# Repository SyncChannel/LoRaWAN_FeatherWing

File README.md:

# LoRaWAN_FeatherWing
Add the MicroChip RN2483/RN2903 LoRaWAN module to Adafruit Feather

http://syncchannel.blogspot.com/2016/06/lorawan-featherwing-for-adafruit-feather.html

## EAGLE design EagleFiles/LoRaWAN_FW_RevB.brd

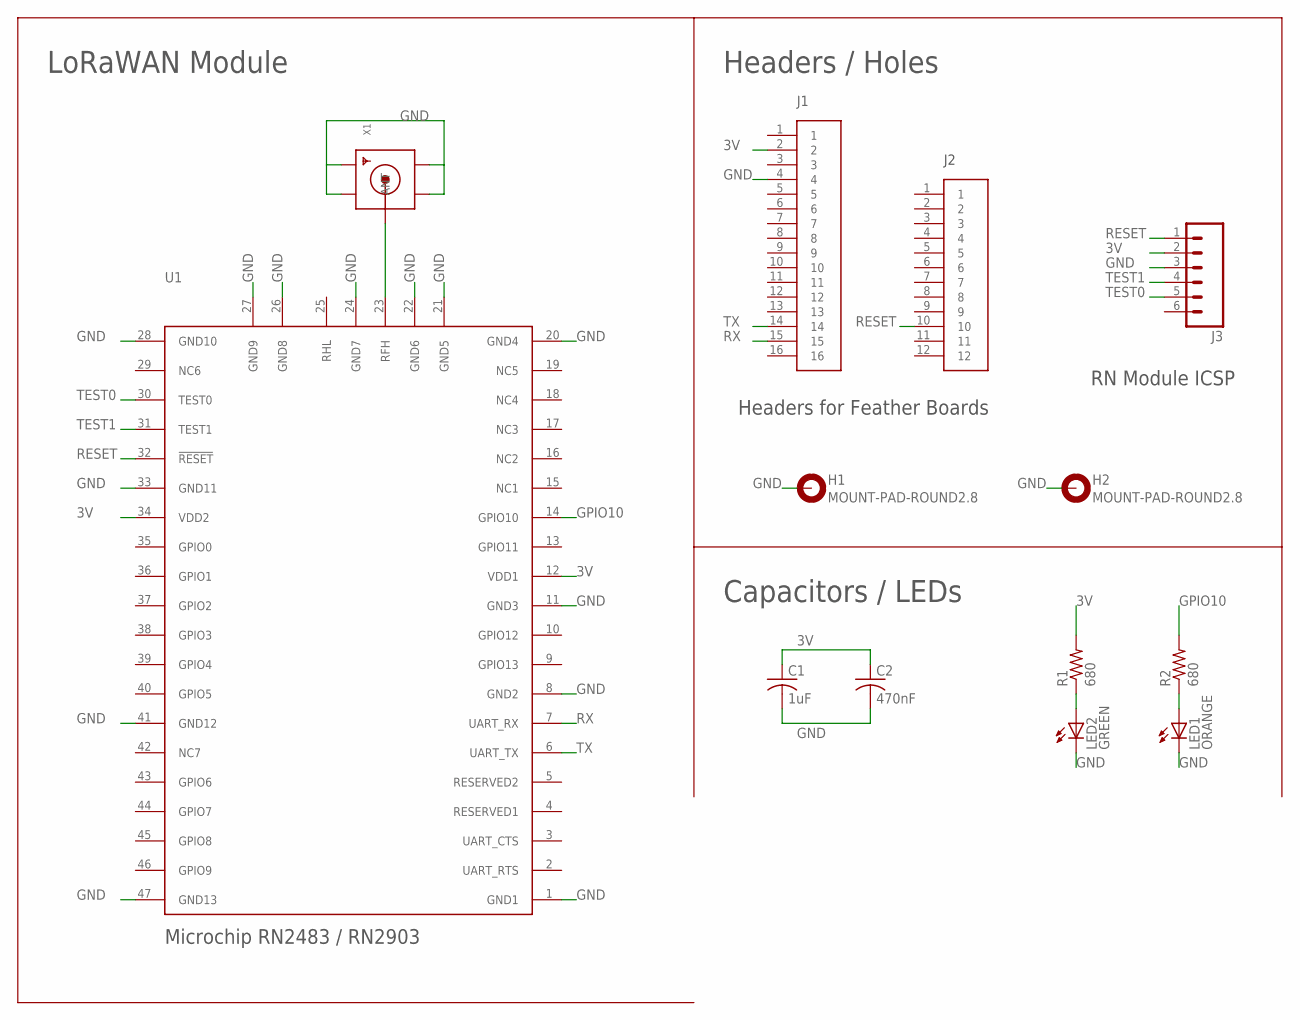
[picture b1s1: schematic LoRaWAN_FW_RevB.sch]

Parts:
C1: 1uF; C0603
C2: 470nF; C0603
H1, H2: MOUNT-PAD-ROUND2.8; 2,8-PAD
J1: 1X16_SMD_HEADER
J2: 1X12_SMD_HEADER
J3: M06SILK_FEMALE_PTH; 1X06
LED1: ORANGE; CHIPLED_0805
LED2: GREEN; CHIPLED_0805
R1, R2: 680; R0603
U1: RN2483/RN2903
X1: SMACONNECTOR_EDGE; SMA_EDGELAUNCH

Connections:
3V: C1.1, C2.1, J1.2, J3.2, R1.2, U1.12 (VDD1), U1.34 (VDD2)
GND: C1.2, C2.2, H1.B2,8, H2.B2,8, J1.4, J3.3, LED1.C, LED2.C, U1.1 (GND1), U1.8 (GND2), U1.11 (GND3), U1.20 (GND4), U1.21 (GND5), U1.22 (GND6), U1.24 (GND7), U1.26 (GND8), U1.27 (GND9), U1.28 (GND10), U1.33 (GND11), U1.41 (GND12), U1.47 (GND13), X1.GND@1 (GND4), X1.GND@2 (GND3), X1.GND@3 (GND2), X1.GND@4 (GND1)
GPIO10: R2.2, U1.14 (GPIO10)
unnamed: LED1.A, R2.1
unnamed: U1.23 (RFH), X1.P (ANT)
unnamed: LED2.A, R1.1
RESET: J2.10, J3.1, U1.32 (!RESET)
RX: J1.15, U1.7 (UART_RX)
TEST0: J3.5, U1.30 (TEST0)
TEST1: J3.4, U1.31 (TEST1)
TX: J1.14, U1.6 (UART_TX)

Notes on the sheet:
Headers for Feather Boards
Headers / Holes
Capacitors / LEDs
RN Module ICSP
LoRaWAN Module
Microchip RN2483 / RN2903

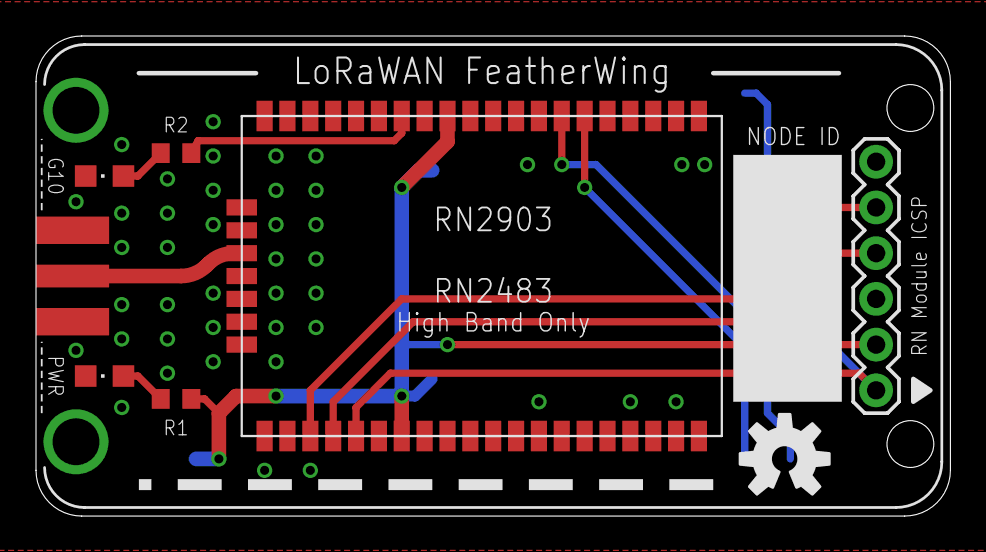
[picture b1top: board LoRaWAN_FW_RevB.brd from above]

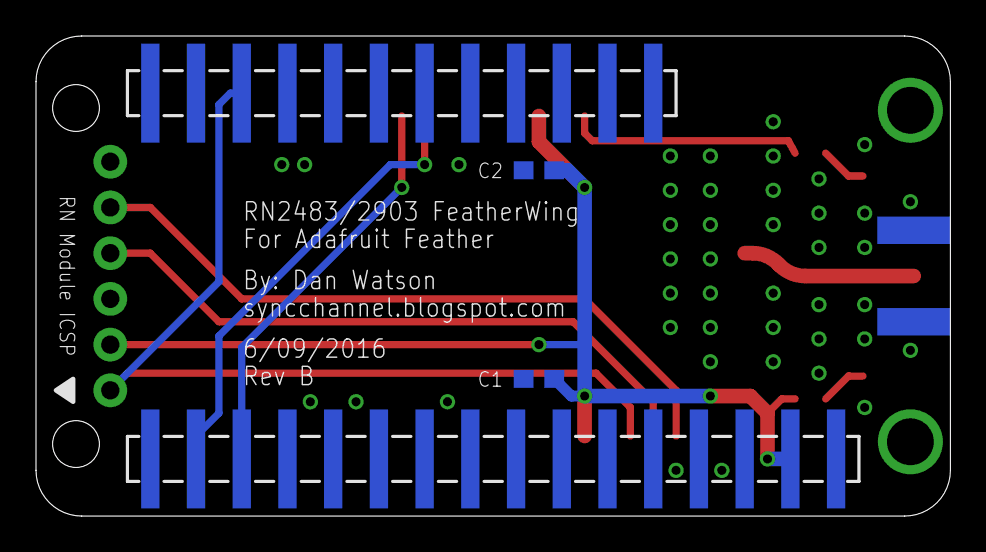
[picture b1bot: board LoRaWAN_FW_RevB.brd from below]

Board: 2 copper layers, 50.8 x 26.7 mm, 14 parts (4 on the bottom side), 11 nets.

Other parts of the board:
U$1: OSHW-LOGO-M

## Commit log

2016-06-26 :space_invader: Added .gitattributes & .gitignore files
2016-06-26 Added Eagle Files
2016-06-26 Create License file
2016-06-27 Added project link
2016-06-27 Updated Eagle files

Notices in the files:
parts and their libraries:
SparkFun-Aesthetics: Licensing: Creative Commons ShareAlike 4.0 International - https://creativecommons.org/licenses/by-sa/4.0
